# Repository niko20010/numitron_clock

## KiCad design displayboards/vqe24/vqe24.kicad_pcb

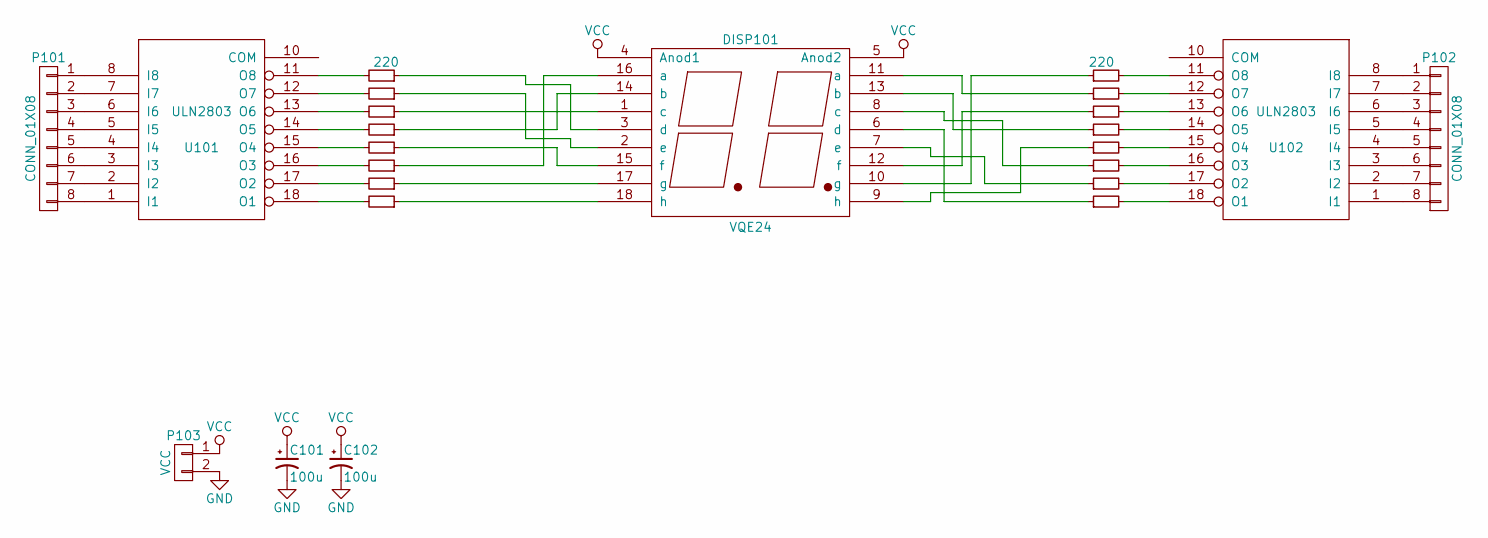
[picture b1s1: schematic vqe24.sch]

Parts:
C101, C102: 100u; TantalC_SizeD_EIA-7343_HandSoldering
DISP101: VQE24; DA56
P101, P102: CONN_01X08; Pin_Header_Straight_1x08
P103: VCC; Pin_Header_Straight_1x02_Pitch3.96mm_Friction_Lock
R101, R102, R103, R104, R105, R106, R107, R108, R109, R110, R111, R112, R113, R114, R115, R116: 220; R_1206_HandSoldering
U101, U102: ULN2803; DIP-18_W7.62mm

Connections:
GND: C101.2, C102.2, P103.2, U101.9 (GND), U102.9 (GND)
unnamed: DISP101.1 (c), R105.1
unnamed: DISP101.2 (e), R103.1
unnamed: DISP101.3 (d), R101.1
unnamed: DISP101.6 (d), R116.1
unnamed: DISP101.7 (e), R114.1
unnamed: DISP101.8 (c), R112.1
unnamed: DISP101.9 (h), R110.1
unnamed: DISP101.10 (g), R102.1
unnamed: DISP101.11 (a), R104.1
unnamed: DISP101.12 (f), R106.1
unnamed: DISP101.13 (b), R108.1
unnamed: DISP101.14 (b), R107.1
unnamed: DISP101.15 (f), R109.1
unnamed: DISP101.16 (a), R111.1
unnamed: DISP101.17 (g), R113.1
unnamed: DISP101.18 (h), R115.1
unnamed: P101.1, U101.8 (I8)
unnamed: P101.2, U101.7 (I7)
unnamed: P101.3, U101.6 (I6)
unnamed: P101.4, U101.5 (I5)
unnamed: P101.5, U101.4 (I4)
unnamed: P101.6, U101.3 (I3)
unnamed: P101.7, U101.2 (I2)
unnamed: P101.8, U101.1 (I1)
unnamed: P102.1, U102.8 (I8)
unnamed: P102.2, U102.7 (I7)
unnamed: P102.3, U102.6 (I6)
unnamed: P102.4, U102.5 (I5)
unnamed: P102.5, U102.4 (I4)
unnamed: P102.6, U102.3 (I3)
unnamed: P102.7, U102.2 (I2)
unnamed: P102.8, U102.1 (I1)
unnamed: R101.2, U101.11 (O8)
unnamed: R102.2, U102.11 (O8)
unnamed: R103.2, U101.12 (O7)
unnamed: R104.2, U102.12 (O7)
unnamed: R105.2, U101.13 (O6)
unnamed: R106.2, U102.13 (O6)
unnamed: R107.2, U101.14 (O5)
unnamed: R108.2, U102.14 (O5)
unnamed: R109.2, U101.15 (O4)
unnamed: R110.2, U102.15 (O4)
unnamed: R111.2, U101.16 (O3)
unnamed: R112.2, U102.16 (O3)
unnamed: R113.2, U101.17 (O2)
unnamed: R114.2, U102.17 (O2)
unnamed: R115.2, U101.18 (O1)
unnamed: R116.2, U102.18 (O1)
VCC: C101.1, C102.1, DISP101.4 (Anod1), DISP101.5 (Anod2), P103.1

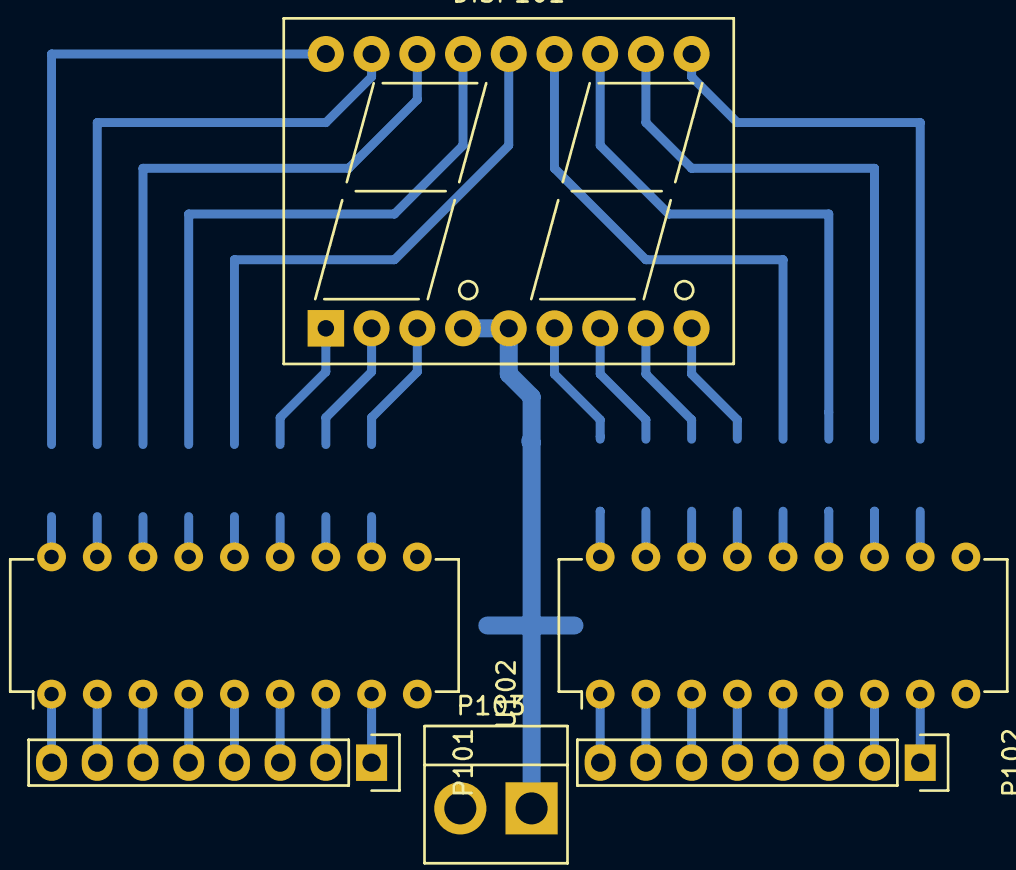
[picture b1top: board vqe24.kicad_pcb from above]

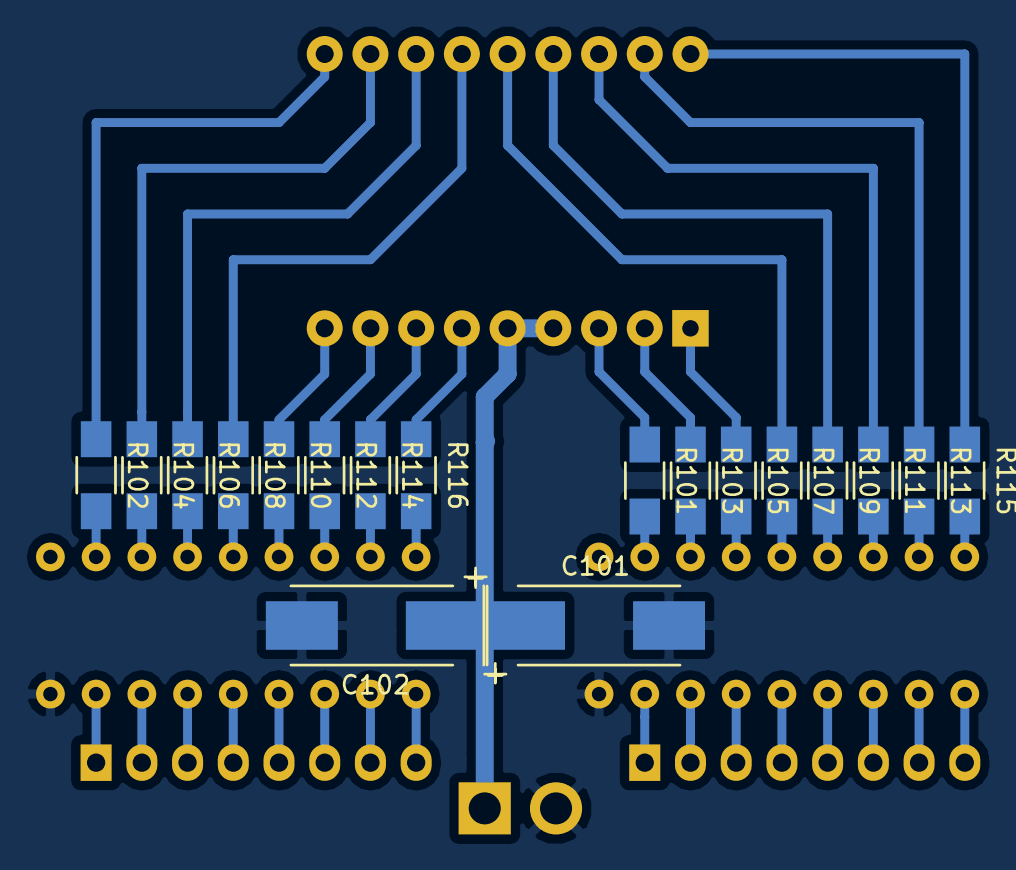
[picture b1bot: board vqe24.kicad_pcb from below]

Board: 2 copper layers, 24 parts (18 on the bottom side), 50 nets.

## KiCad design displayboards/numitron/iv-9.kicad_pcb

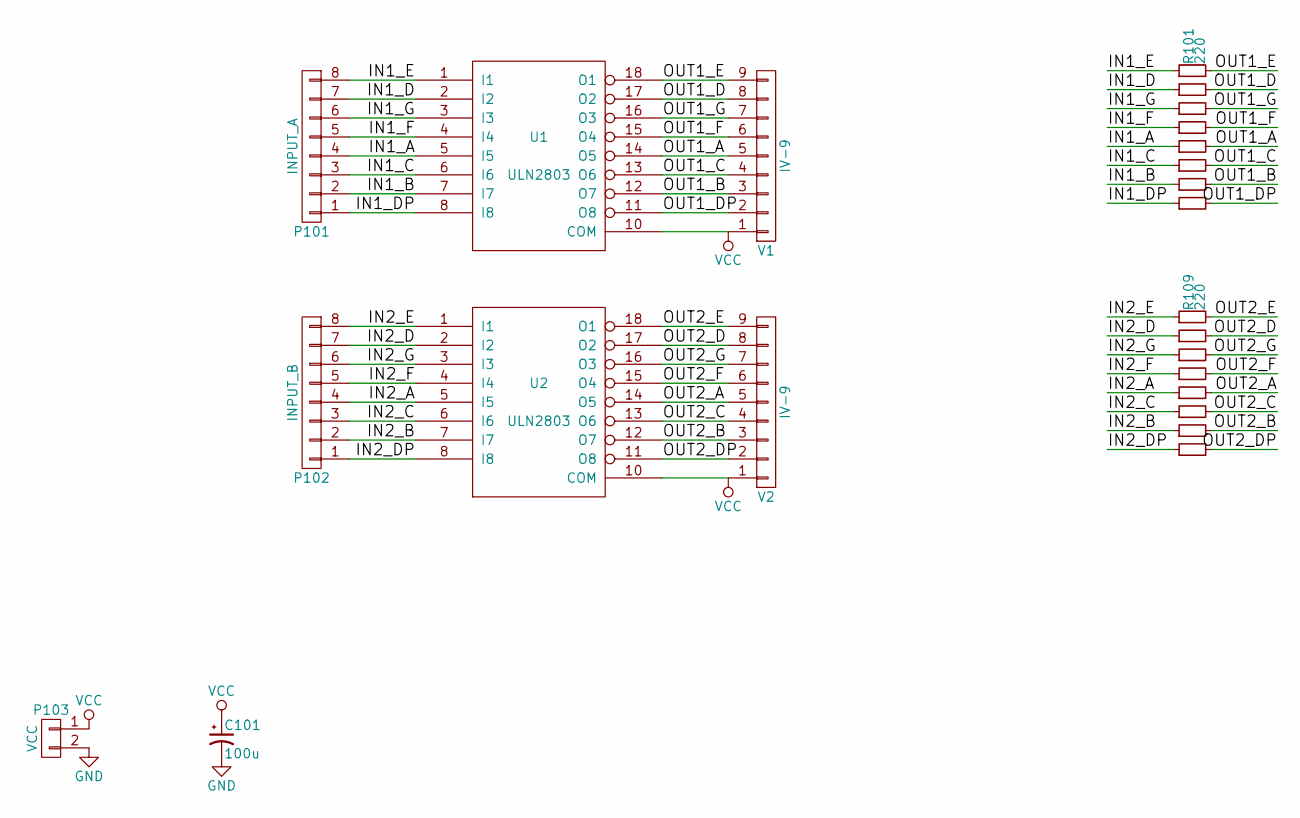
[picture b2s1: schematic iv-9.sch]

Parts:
C101: 100u; TantalC_SizeD_EIA-7343_HandSoldering
P101: INPUT_A; Pin_Header_Straight_1x08
P102: INPUT_B; Pin_Header_Straight_1x08
P103: VCC; Pin_Header_Straight_1x02_Pitch3.96mm_Friction_Lock
R101, R102, R103, R104, R105, R106, R107, R108, R109, R110, R111, R112, R113, R114, R115, R116: 220; R_1206_HandSoldering
U1, U2: ULN2803; DIP-18_W7.62mm
V1, V2: IV-9; VALVE-IV-9

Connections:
/IN1_A: P101.4, R105.1, U1.5 (I5)
/IN1_B: P101.2, R107.1, U1.7 (I7)
/IN1_C: P101.3, R106.1, U1.6 (I6)
/IN1_D: P101.7, R102.1, U1.2 (I2)
/IN1_DP: P101.1, R108.1, U1.8 (I8)
/IN1_E: P101.8, R101.1, U1.1 (I1)
/IN1_F: P101.5, R104.1, U1.4 (I4)
/IN1_G: P101.6, R103.1, U1.3 (I3)
/IN2_A: P102.4, R113.1, U2.5 (I5)
/IN2_B: P102.2, R115.1, U2.7 (I7)
/IN2_C: P102.3, R114.1, U2.6 (I6)
/IN2_D: P102.7, R110.1, U2.2 (I2)
/IN2_DP: P102.1, R116.1, U2.8 (I8)
/IN2_E: P102.8, R109.1, U2.1 (I1)
/IN2_F: P102.5, R112.1, U2.4 (I4)
/IN2_G: P102.6, R111.1, U2.3 (I3)
/OUT1_A: R105.2, U1.14 (O5), V1.5
/OUT1_B: R107.2, U1.12 (O7), V1.3
/OUT1_C: R106.2, U1.13 (O6), V1.4
/OUT1_D: R102.2, U1.17 (O2), V1.8
/OUT1_DP: R108.2, U1.11 (O8), V1.2
/OUT1_E: R101.2, U1.18 (O1), V1.9
/OUT1_F: R104.2, U1.15 (O4), V1.6
/OUT1_G: R103.2, U1.16 (O3), V1.7
/OUT2_A: R113.2, U2.14 (O5), V2.5
/OUT2_B: R115.2, U2.12 (O7), V2.3
/OUT2_C: R114.2, U2.13 (O6), V2.4
/OUT2_D: R110.2, U2.17 (O2), V2.8
/OUT2_DP: R116.2, U2.11 (O8), V2.2
/OUT2_E: R109.2, U2.18 (O1), V2.9
/OUT2_F: R112.2, U2.15 (O4), V2.6
/OUT2_G: R111.2, U2.16 (O3), V2.7
GND: C101.2, P103.2, U1.9 (GND), U2.9 (GND)
VCC: C101.1, P103.1, U1.10 (COM), U2.10 (COM), V1.1, V2.1

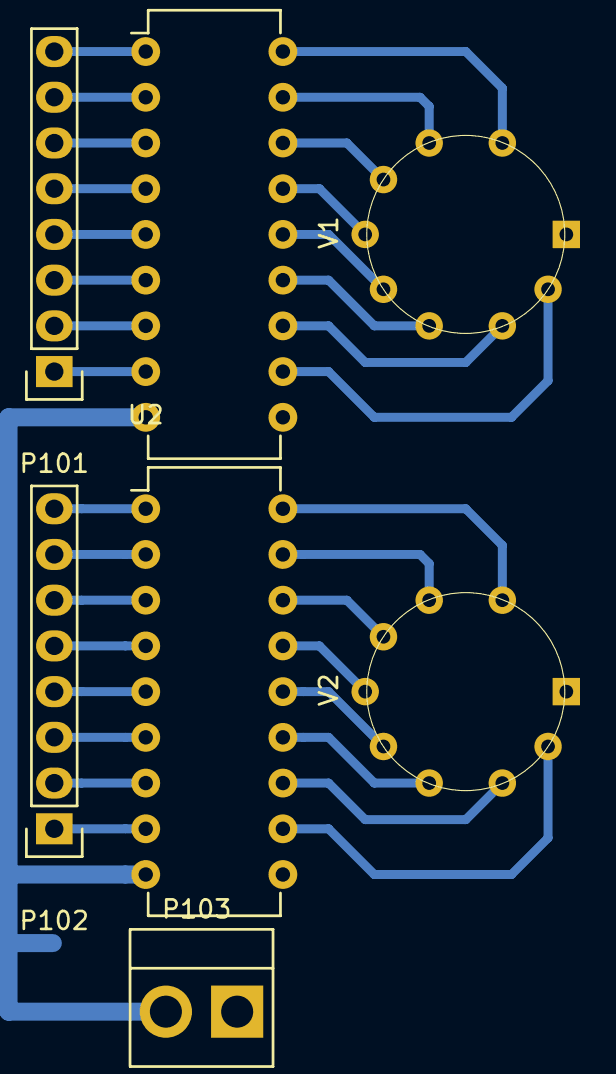
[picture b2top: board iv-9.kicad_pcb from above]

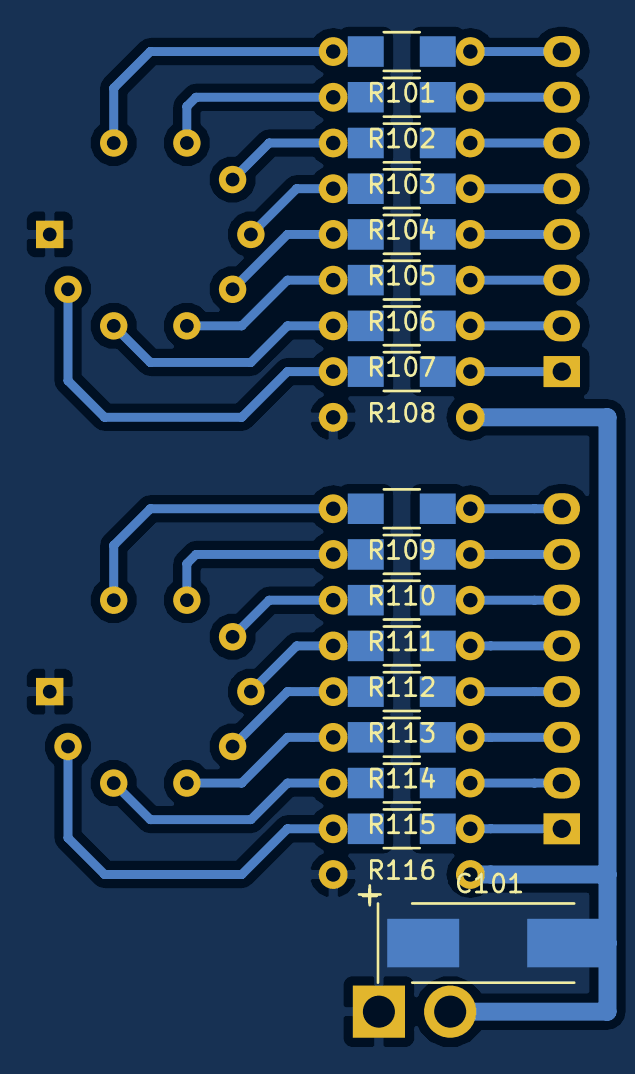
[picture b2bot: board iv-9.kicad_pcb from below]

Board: 2 copper layers, 24 parts (17 on the bottom side), 34 nets.

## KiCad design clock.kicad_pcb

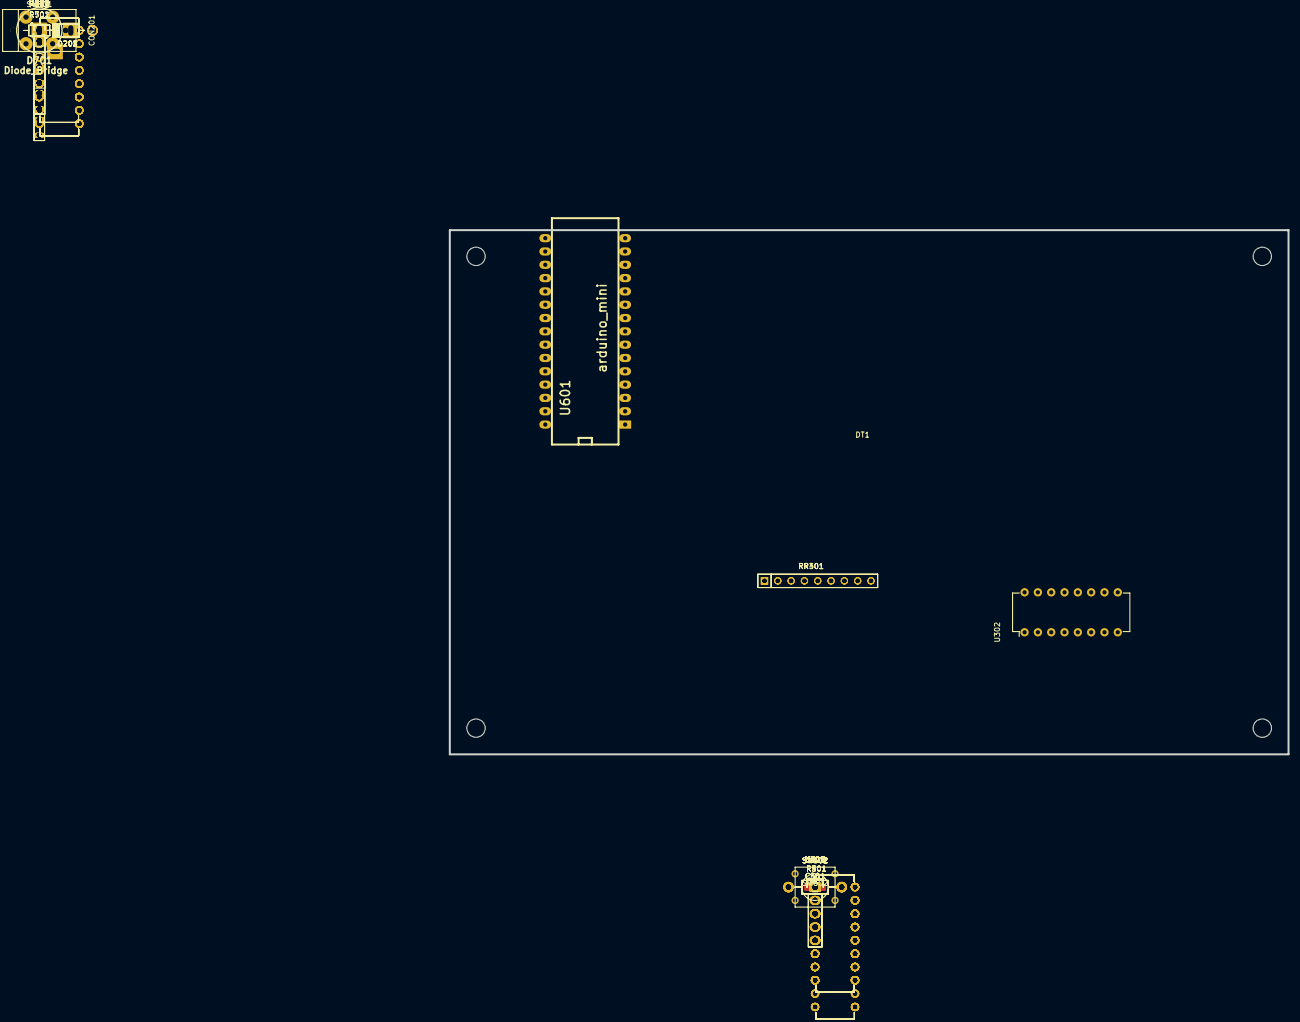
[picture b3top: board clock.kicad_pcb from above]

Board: 2 copper layers, 160.0 x 100.0 mm, 55 parts (0 on the bottom side), 129 nets, no tracks yet.

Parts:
C301, C401, C501: 100n; C_0805_HandSoldering
CON201: BARREL_JACK
D201, D202, D203, D204: D; Diode_DO-41_SOD81_Horizontal_RM10
D701: Diode_Bridge; bridge_wob
DT1: DETAIL; EuroBoard160mmX100mm_holes
P201: CONN_01X05; Pin_Header_Straight_1x05
P202, P203, P301, P302, P402, P403: CONN_01X07; Pin_Header_Straight_1x07
P401, P501: CONN_01X09; Pin_Header_Straight_1x09
R301, R401, R501, R502: 10k; Resistor_Horizontal_RM10mm
R701: 15k; Resistor_Horizontal_RM10mm
RR301, RR401: RR8; Resistor_Array_SIP8
SW301, SW302, SW401, SW402: Coded_Switch; Pin_Header_Straight_1x05
SW501: SPST; Pin_Header_Straight_1x02
SW602: SW_PUSH_SMALL_H; SW_PUSH_SMALL
U101, U401: 4011; DIP-14_W7.62mm
U201, U202, U301, U303, U403, U406: 4511; DIP-16_W7.62mm
U302, U304, U402, U404, U502, U504: 4510; DIP-16_W7.62mm
U305, U505: 4538; DIP-16_W7.62mm
U306, U307, U405: 74LS688; DIP-20_W7.62mm
U601: arduino_mini
U602, U603, U604: 4017; DIP-16_W7.62mm

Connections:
+5V: D201.2, R301.1, R401.1, R501.1, R502.1, SW301.1, SW302.1, SW401.1, SW402.1, U101.14, U201.3, U201.4, U201.16, U202.3, U202.4, U202.16, U301.3, U301.4, U301.16, U302.10, U302.16, U303.3, U303.4, U303.16, U304.10, U304.16, U305.3, U305.13, U305.16, U306.20, U307.7, U307.14, U307.20, U401.14, U402.10, U402.16, U403.3, U403.4, U403.16, U404.10, U404.16, U405.20, U406.3, U406.4, U406.16, U502.10, U502.16, U504.10, U504.16, U505.3, U505.16, U601.12, U602.16, U603.16, U604.15, U604.16
+9V: D701.3, U601.15
/Hours/CIN: U101.10, U302.15, U305.11
/Hours/COUT: U305.5, U307.19, U601.21
/Hours/LOAD_1s: U302.1, U602.1
/Hours/LOAD_10s: U304.1, U602.5
/Hours/RST: U302.9, U304.9, U305.6
/Hours/~ALARM_MATCH: U101.5, U101.6, U306.19
/MCU/ALARM_IN: U101.11, U601.20
/Minutes/CIN: U401.3, U402.15, U505.5
/Minutes/LOAD_1s: U402.1, U602.7
/Minutes/LOAD_10s: U404.1, U602.10
/Minutes/RST: U305.10, U402.9, U404.9
/Minutes/~ALARM_MATCH: U101.1, U101.2, U405.19
/Powersupply/CLK_50: R701.1, U603.14
/Seconds/CIN: U502.15, U604.3
/Seconds/LOAD_1s: U502.1, U602.2
/Seconds/LOAD_10s: U504.1, U602.4
/Seconds/RST: U502.9, U504.9, U505.6
A1: U302.4, U304.4, U402.4, U404.4, U502.4, U504.4, U601.22
A2: U302.12, U304.12, U402.12, U404.12, U502.12, U504.12, U601.23
A3: U302.13, U304.13, U402.13, U404.13, U502.13, U504.13, U601.24
A4: U302.3, U304.3, U402.3, U404.3, U502.3, U504.3, U601.25
GND: D701.1, RR301.1, RR401.1, SW501.1, SW602.1, U101.7, U201.5, U201.8, U202.5, U202.8, U301.5, U301.8, U302.5, U302.8, U303.5, U303.8, U304.5, U304.8, U305.4, U305.8, U305.12, U306.10, U307.1, U307.3, U307.5, U307.9, U307.10, U307.12, U307.16, U307.18, U401.7, U402.5, U402.8, U403.5, U403.8, U404.5, U404.8, U405.10, U406.5, U406.8, U502.5, U502.8, U504.5, U504.8, U505.4, U505.8, U601.14, U601.19, U602.8, U602.13, U603.8, U603.13, U604.8, U604.13
unnamed: C301.1, R301.2, U305.2
unnamed: C301.2, U305.1
unnamed: C401.1, R401.2, U305.14
unnamed: C401.2, U305.15
unnamed: C501.1, R501.2, U505.2
unnamed: C501.2, U505.1
unnamed: CON201.1, D701.4, R701.2
unnamed: CON201.2, CON201.3, D701.2
unnamed: D201.1, D202.2, P201.2
unnamed: D202.1, D203.2, P201.3
unnamed: D203.1, D204.2, P201.4
unnamed: D204.1, P201.5
unnamed: P202.1, U201.13
unnamed: P202.2, U201.12
unnamed: P202.3, U201.11
unnamed: P202.4, U201.10
unnamed: P202.5, U201.9
unnamed: P202.6, U201.15
unnamed: P202.7, U201.14
unnamed: P203.1, U202.13
unnamed: P203.2, U202.12
unnamed: P203.3, U202.11
unnamed: P203.4, U202.10
unnamed: P203.5, U202.9
unnamed: P203.6, U202.15
unnamed: P203.7, U202.14
unnamed: P301.1, U301.13
unnamed: P301.2, U301.12
unnamed: P301.3, U301.11
unnamed: P301.4, U301.10
unnamed: P301.5, U301.9
unnamed: P301.6, U301.15
unnamed: P301.7, U301.14
unnamed: P302.1, U303.13
unnamed: P302.2, U303.12
unnamed: P302.3, U303.11
unnamed: P302.4, U303.10
unnamed: P302.5, U303.9
unnamed: P302.6, U303.15
unnamed: P302.7, U303.14
unnamed: P401.2, U301.7, U402.6, U405.2
unnamed: P401.3, U301.1, U402.11, U405.4
unnamed: P401.4, U301.2, U402.14, U405.6
unnamed: P401.5, U301.6, U402.2, U405.8
unnamed: P401.6, U303.7, U404.6, U405.11
unnamed: P401.7, U101.8, U303.1, U404.11, U405.13
unnamed: P401.8, U101.9, U303.2, U404.14, U405.15
unnamed: P401.9, U303.6, U404.2, U405.17
unnamed: P402.1, U403.13
unnamed: P402.2, U403.12
unnamed: P402.3, U403.11
unnamed: P402.4, U403.10
unnamed: P402.5, U403.9
unnamed: P402.6, U403.15
unnamed: P402.7, U403.14
unnamed: P403.1, U406.13
unnamed: P403.2, U406.12
unnamed: P403.3, U406.11
unnamed: P403.4, U406.10
unnamed: P403.5, U406.9
unnamed: P403.6, U406.15
unnamed: P403.7, U406.14
unnamed: P501.2, U403.7, U502.6
unnamed: P501.3, U403.1, U502.11
unnamed: P501.4, U403.2, U502.14
unnamed: P501.5, U403.6, U502.2
unnamed: P501.6, U406.7, U504.6
unnamed: P501.7, U401.1, U406.1, U504.11
unnamed: P501.8, U401.2, U406.2, U504.14
unnamed: P501.9, U504.2
unnamed: RR301.2, SW302.5, U306.18
unnamed: RR301.3, SW302.4, U306.16
unnamed: RR301.4, SW302.3, U306.14
unnamed: RR301.5, SW302.2, U306.12
unnamed: RR301.6, SW301.5, U306.9
unnamed: RR301.7, SW301.4, U306.7
unnamed: RR301.8, SW301.3, U306.5
unnamed: RR301.9, SW301.2, U306.3
unnamed: RR401.2, SW402.5, U405.18
unnamed: RR401.3, SW402.4, U405.16
unnamed: RR401.4, SW402.3, U405.14
unnamed: RR401.5, SW402.2, U405.12
unnamed: RR401.6, SW401.5, U405.9
unnamed: RR401.7, SW401.4, U405.7
unnamed: RR401.8, SW401.3, U405.5
unnamed: RR401.9, SW401.2, U405.3
unnamed: SW602.2, U601.13
unnamed: U101.4, U101.12
unnamed: U101.3, U101.13
unnamed: U201.1, U302.11, U306.4, U307.4
unnamed: U201.2, U302.14, U306.6, U307.6
unnamed: U201.6, U302.2, U306.8, U307.8
unnamed: U201.7, U302.6, U306.2, U307.2
unnamed: U202.1, U304.11, U306.13, U307.13
unnamed: U202.2, U304.14, U306.15, U307.15
unnamed: U202.6, U304.2, U306.17, U307.17
unnamed: U202.7, U304.6, U306.11, U307.11
unnamed: U302.7, U304.15
unnamed: U402.7, U404.15
unnamed: U502.7, U504.15
unnamed: U601.26, U602.15
unnamed: U601.27, U602.14
unnamed: U603.12, U604.14
VAA: P201.1, P401.1, P501.1
~ALARM_EN: R502.2, SW501.2, U306.1, U405.1

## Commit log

2016-11-01 first CMOS version
2016-11-02 removed BCD decoders
2016-11-08 switched clocksource to 50Hz mains frequency
2016-11-08 revised clock generator
2016-11-12 some revisions
